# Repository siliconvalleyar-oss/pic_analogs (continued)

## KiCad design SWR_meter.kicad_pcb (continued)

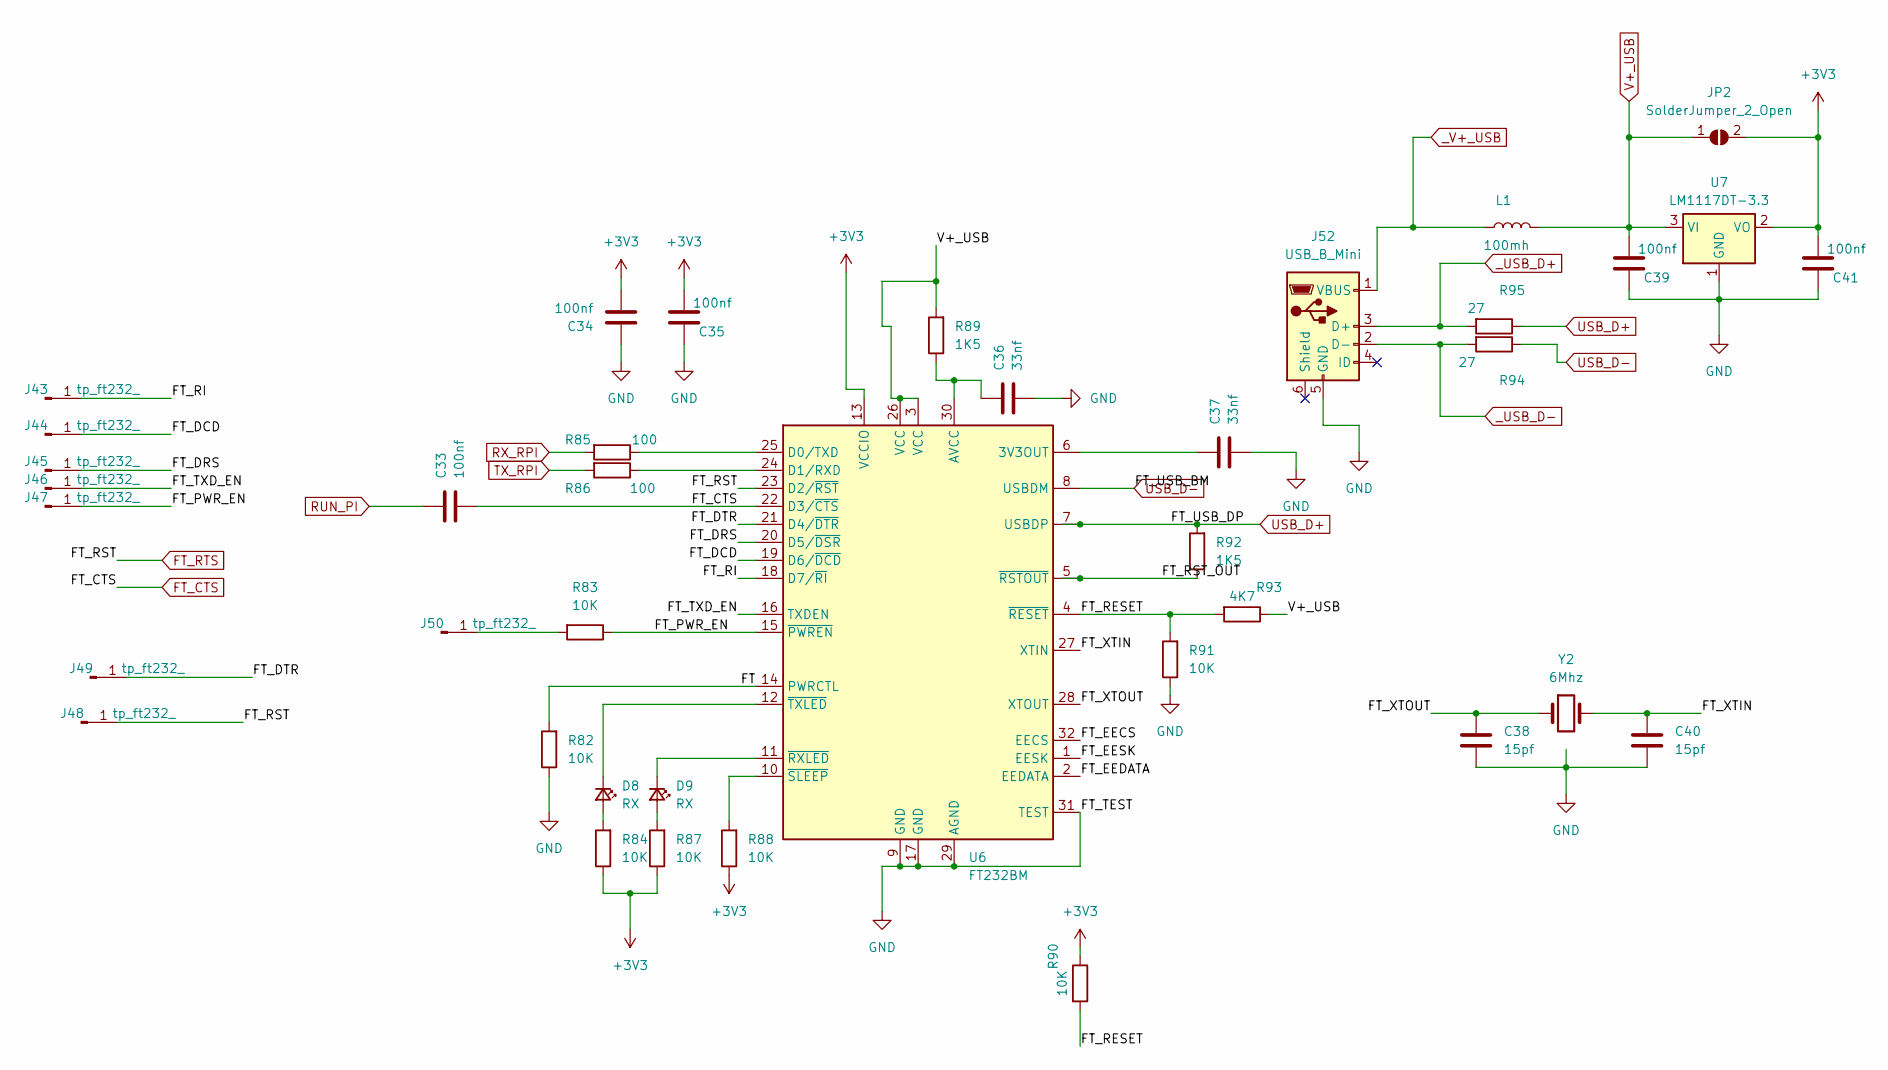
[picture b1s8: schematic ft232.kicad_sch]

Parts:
C33: 100nf; C_0805_2012Metric
C34, C35, C39, C41: 100nf; C_0603_1608Metric
C36, C37: 33nf; C_0603_1608Metric
C38, C40: 15pf; C_0805_2012Metric
D8, D9: RX; D_0603_1608Metric
J43, J44, J45, J46, J47, J48, J49, J50: tp_ft232_; TestPoint_Pad_1.0x1.0mm
J52: USB_B_Mini; USB_Mini-B_Wuerth_65100516121_Horizontal
JP2: SolderJumper_2_Open; SolderJumper-2_P1.3mm_Open_TrianglePad1.0x1.5mm
L1: 100mh; L_6.3x6.3_H3
R82, R83, R84, R88, R90, R91: 10K; R_0603_1608Metric
R85, R86: 100; R_0603_1608Metric
R87: 10K; R_0805_2012Metric
R89, R92: 1K5; R_0603_1608Metric
R93: 4K7; R_0603_1608Metric
R94, R95: 27; R_0805_2012Metric
U6: FT232BM; LQFP-32_7x7mm_P0.8mm
U7: LM1117DT-3.3; TO-252-3_TabPin2
Y2: 6Mhz; Crystal_HC49-U_Vertical

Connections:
+3V3: C34.2, C35.2, C41.2, JP2.2 (B), R84.1, R87.1, R88.1, R90.1, U6.13 (VCCIO), U7.2 (VO); also elsewhere on the board
/magnetics/mcu_pic/rpi/ft232/FT: R82.2, U6.14 (PWRCTL)
/magnetics/mcu_pic/rpi/ft232/FT_DCD: J44.1 (Pin_1_1), U6.19 (D6/~DCD)
/magnetics/mcu_pic/rpi/ft232/FT_DRS: J45.1 (Pin_1_1), U6.20 (D5/~DSR)
/magnetics/mcu_pic/rpi/ft232/FT_DTR: J49.1 (Pin_1_1), U6.21 (D4/~DTR)
/magnetics/mcu_pic/rpi/ft232/FT_EECS: U6.32 (EECS)
/magnetics/mcu_pic/rpi/ft232/FT_EEDATA: U6.2 (EEDATA)
/magnetics/mcu_pic/rpi/ft232/FT_EESK: U6.1 (EESK)
/magnetics/mcu_pic/rpi/ft232/FT_PWR_EN: J47.1 (Pin_1_1), R83.1, U6.15 (~PWREN)
/magnetics/mcu_pic/rpi/ft232/FT_RESET: R90.2, R91.2, R93.2, U6.4 (~RESET)
/magnetics/mcu_pic/rpi/ft232/FT_RI: J43.1 (Pin_1_1), U6.18 (D7/~RI)
/magnetics/mcu_pic/rpi/ft232/FT_RST_OUT: R92.1, U6.5 (~RSTOUT)
/magnetics/mcu_pic/rpi/ft232/FT_TXD_EN: J46.1 (Pin_1_1), U6.16 (TXDEN)
/magnetics/mcu_pic/rpi/ft232/FT_XTIN: C40.1, U6.27 (XTIN), Y2.2
/magnetics/mcu_pic/rpi/ft232/FT_XTOUT: C38.1, U6.28 (XTOUT), Y2.1
FT_CTS: C33.2, U6.22 (D3/~CTS)
FT_RTS: J48.1 (Pin_1_1), U6.23 (D2/~RST)
GND: C34.1, C35.1, C36.2, C37.2, C38.2, C39.1, C40.2, C41.1, J52.5 (GND), J52.6 (Shield), R82.1, R91.1, U6.9 (GND), U6.17 (GND), U6.29 (AGND), U6.31 (TEST), U7.1 (GND); also elsewhere on the board
unnamed: D8.2 (A), R84.2
unnamed: D8.1 (K), U6.12 (~TXLED)
unnamed: D9.2 (A), R87.2
unnamed: D9.1 (K), U6.11 (~RXLED)
unnamed: J50.1 (Pin_1_1), R83.2
unnamed: C37.1, U6.6 (3V3OUT)
unnamed: C36.1, R89.1, U6.30 (AVCC)
unnamed: R85.1, U6.25 (D0/TXD)
unnamed: R86.1, U6.24 (D1/RXD)
unnamed: R88.2, U6.10 (~SLEEP)
RUN_PI: C33.1; also elsewhere on the board
RX_RPI: R85.2; also elsewhere on the board
TX_RPI: R86.2; also elsewhere on the board
USB_D+: R92.2, R94.1, U6.7 (USBDP)
USB_D-: R95.1, U6.8 (USBDM)
V+_USB: C39.2, JP2.1 (A), L1.2, R89.2, R93.1, U6.3 (VCC), U6.26 (VCC), U7.3 (VI)
_USB_D+: J52.3 (D+), R94.2
_USB_D-: J52.2 (D-), R95.2
_V+_USB: J52.1 (VBUS), L1.1

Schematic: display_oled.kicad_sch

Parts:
C23, C24, C25: 100n; C_0805_2012Metric
J6: oled128x64; SSD1306_No_Mounting_whitout_Holes
J36: OledSpiST1306; PinHeader_2x03_P2.54mm_Vertical
J37: OledSpiST7789; Adafruit_SSD1306_No_Mounting_Holes_pads
R56, R57: 2k2; R_0603_1608Metric

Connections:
+3V3: C25.1, J6.2, J36.1, J37.2, R56.1, R57.1; also elsewhere on the board
+5V: C23.1, C24.1, J36.2, J36.4; also elsewhere on the board
BLK_OLED_RP2040: J37.7
DC_OLED_RP2040: J37.6
GND: C23.2, C24.2, C25.2, J6.1, J36.6, J37.1; also elsewhere on the board
GPIO19: J37.4; also elsewhere on the board
GPIO26: J37.3; also elsewhere on the board
RES_OLED_RP2040: J37.5
SCL_OLED_RPI: J6.3, J36.5, R56.2
SDA_OLED_RPI: J6.4, J36.3, R57.2

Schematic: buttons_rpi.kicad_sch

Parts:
R76, R77, R78, R79: R_US; R_0603_1608Metric
SW4: mclr; SW_Push_1P1T_NO_CK_KSC6xxJ
SW5, SW7: ra5; SW_Push_1P1T_NO_CK_KSC6xxJ
SW6: ra4; SW_Push_1P1T_NO_CK_KSC6xxJ

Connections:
GND: SW4.1 (C), SW5.1 (C), SW6.1 (C), SW7.1 (C); also elsewhere on the board
GPIO0: R76.1; also elsewhere on the board
GPIO1: R77.1; also elsewhere on the board
GPIO5: R78.1; also elsewhere on the board
GPIO6: R79.1; also elsewhere on the board
unnamed: R76.2, SW4.2 (D)
unnamed: R77.2, SW5.2 (D)
unnamed: R78.2, SW6.2 (D)
unnamed: R79.2, SW7.2 (D)

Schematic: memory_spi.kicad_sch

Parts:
C43: 100n; C_0603_1608Metric
R96, R98, R99: 10K; R_0603_1608Metric
U8: 25LCxxx; SOIC-8_3.9x4.9mm_P1.27mm

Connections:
+3V3: C43.1, R96.1, R99.1, U8.8 (VCC); also elsewhere on the board
/magnetics/mcu_pic/rpi/mrf24j40/MISO_mrf24j40: U8.2 (MISO); also elsewhere on the board
/magnetics/mcu_pic/rpi/mrf24j40/MOSI_mrf24j40: U8.5 (MOSI); also elsewhere on the board
/magnetics/mcu_pic/rpi/mrf24j40/SCLK_mrf24j40: U8.6 (SCK); also elsewhere on the board
CE1: R96.2, U8.1 (~CS); also elsewhere on the board
GND: C43.2, R98.2, U8.4 (GND); also elsewhere on the board
unnamed: R98.1, U8.7 (~HOLD)
unnamed: R99.2, U8.3 (~WP)

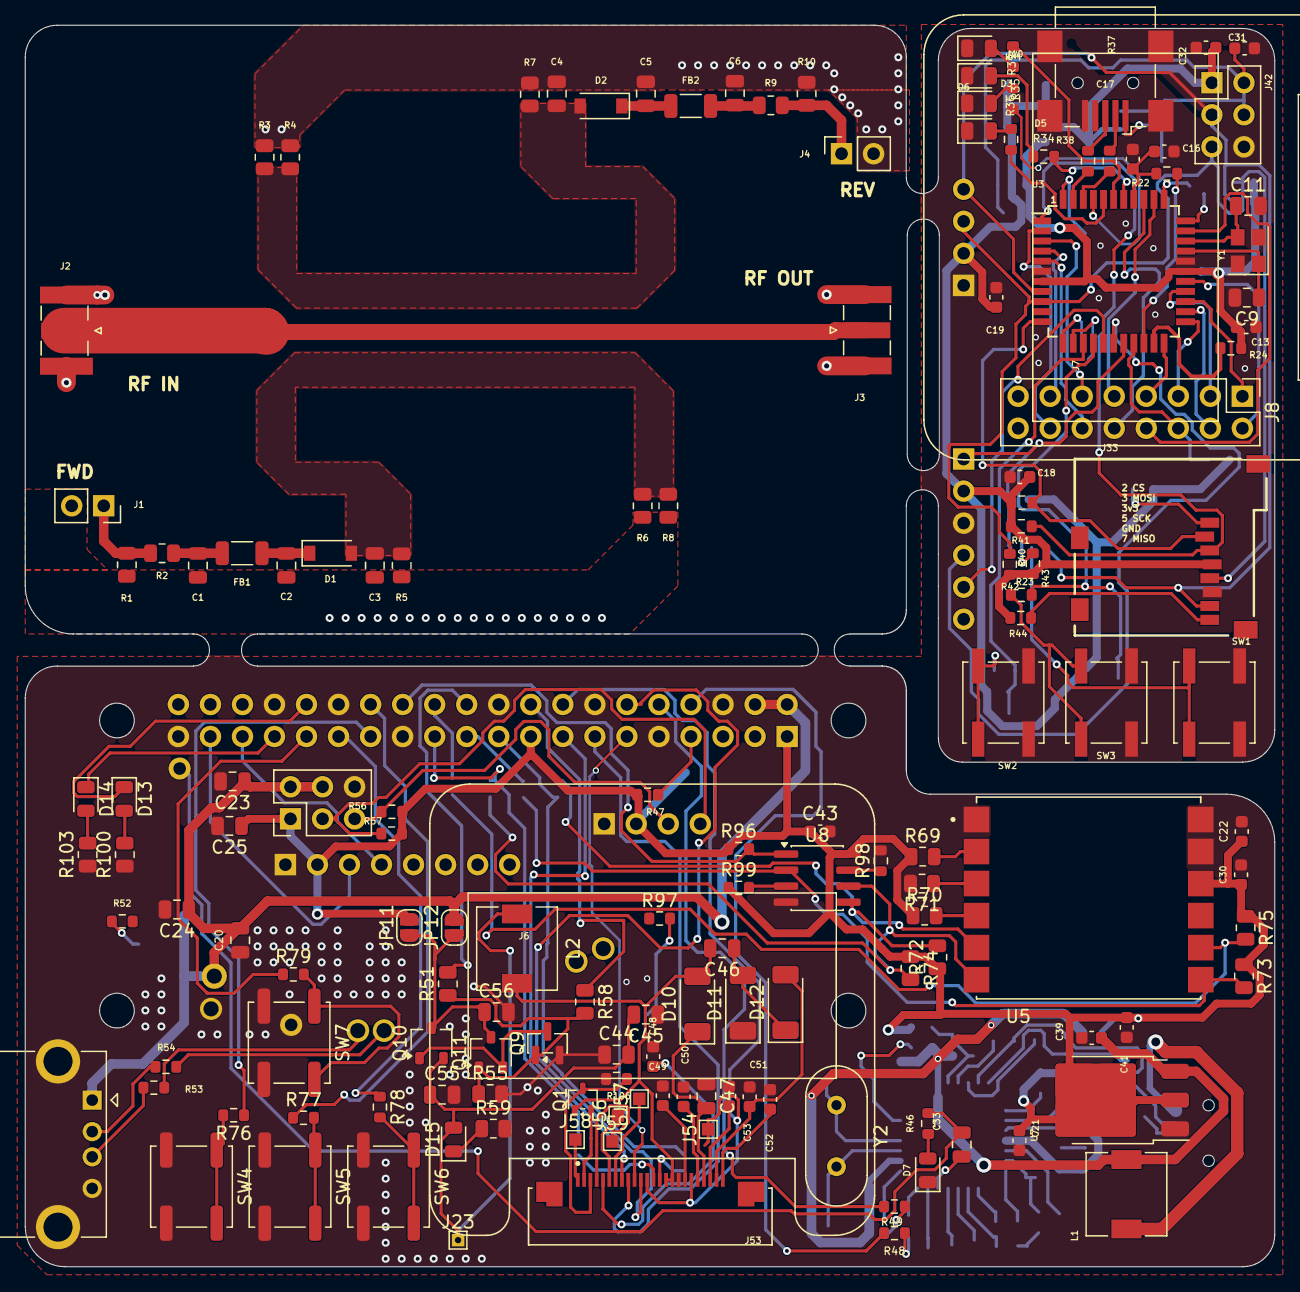
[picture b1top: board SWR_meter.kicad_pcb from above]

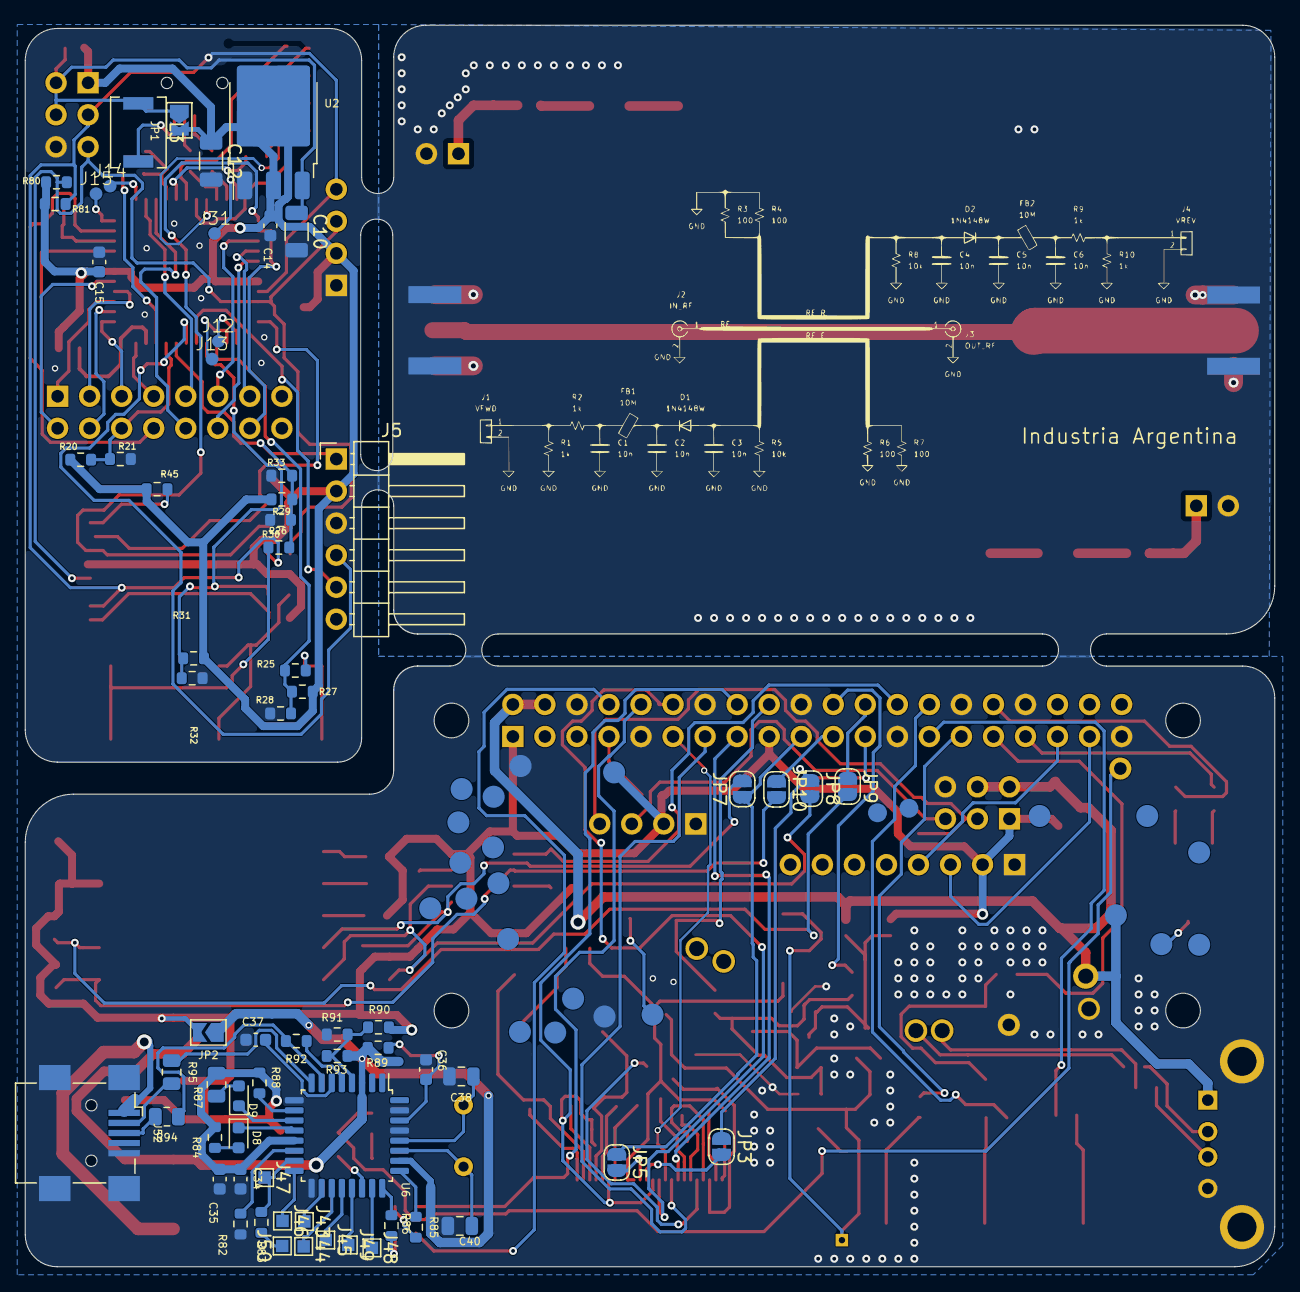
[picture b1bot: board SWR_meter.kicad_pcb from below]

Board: 4 copper layers, 99.1 x 98.4 mm, 216 parts (66 on the bottom side), 166 nets.
